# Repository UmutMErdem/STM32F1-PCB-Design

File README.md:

# STM32F1-PCB-Design
In this repo, there is a STM32F103 PCB design project that I developed on KiCad for educational purposes.

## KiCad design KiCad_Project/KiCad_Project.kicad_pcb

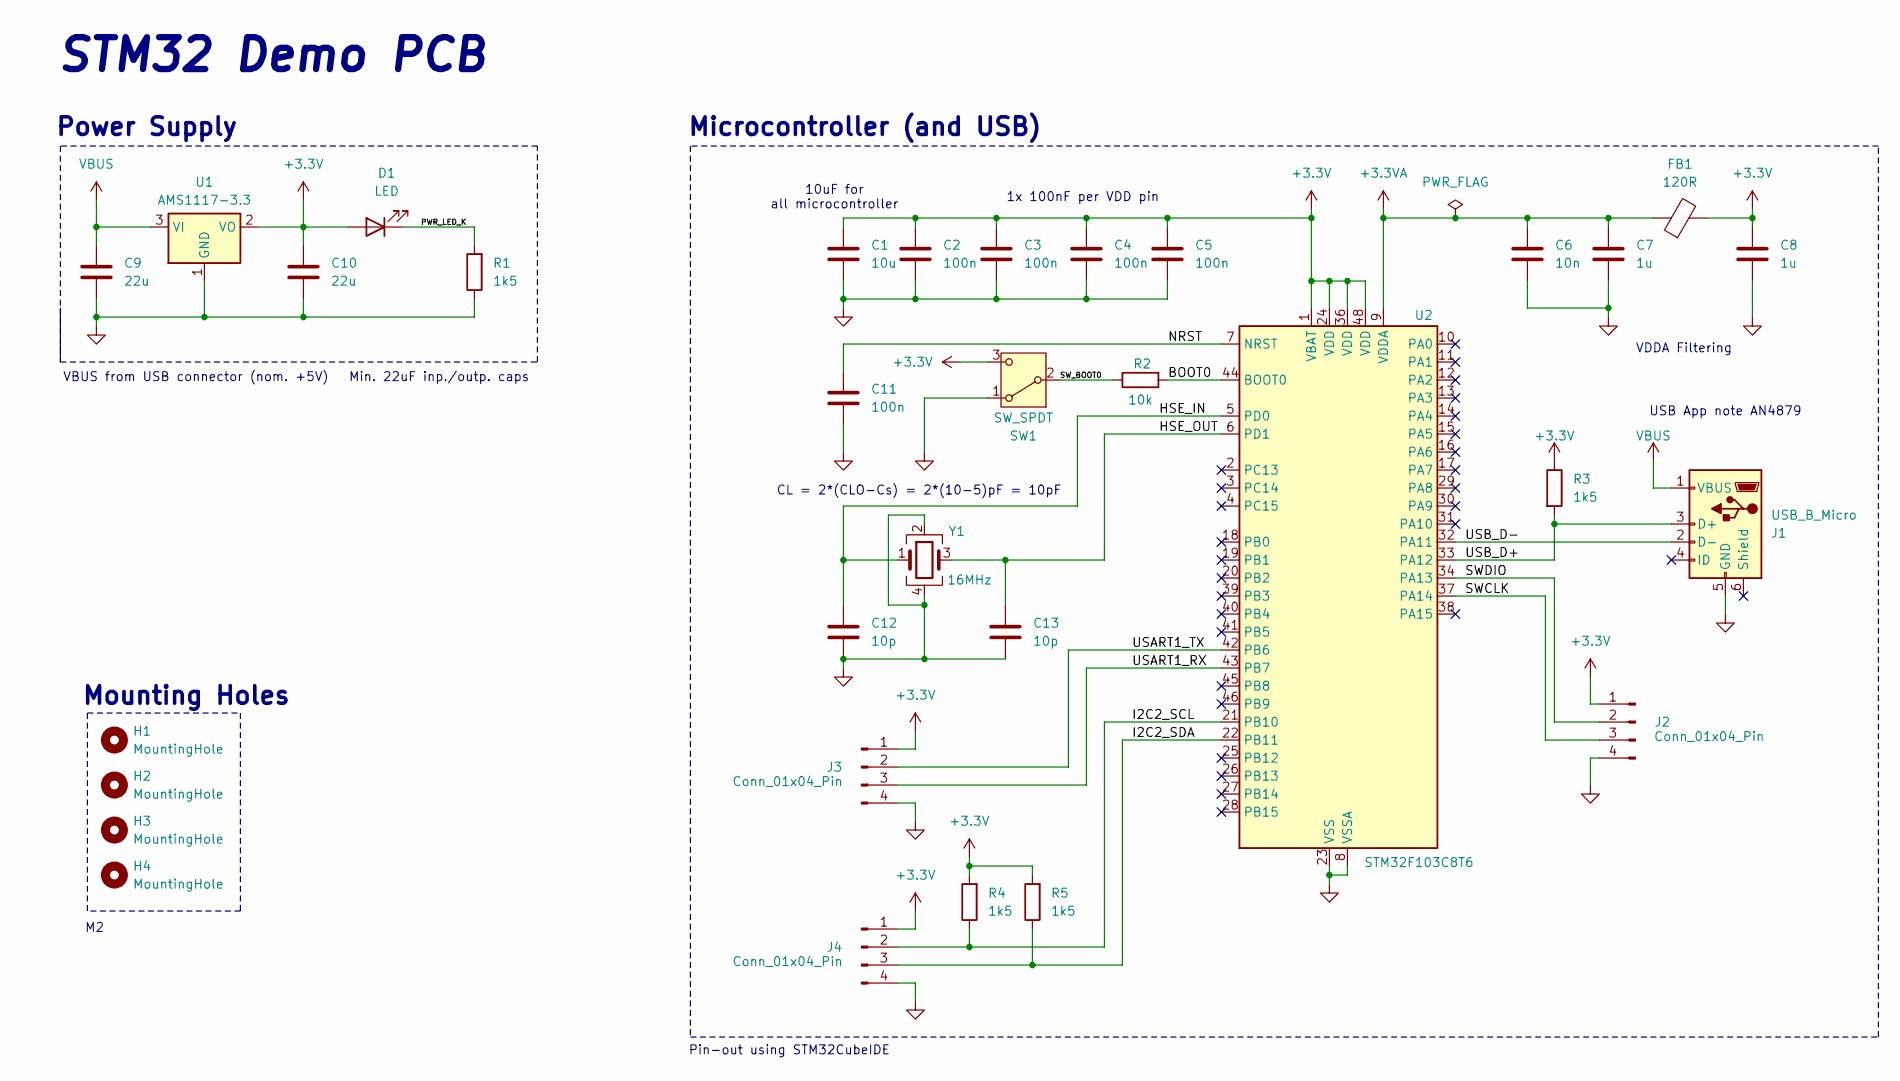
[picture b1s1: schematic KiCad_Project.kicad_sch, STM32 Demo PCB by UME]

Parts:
C1: 10u; C_0603_1608Metric
C2, C3, C4, C5, C11: 100n; C_0402_1005Metric
C6: 10n; C_0402_1005Metric
C7, C8: 1u; C_0402_1005Metric
C9, C10: 22u; C_0805_2012Metric
C12, C13: 10p; C_0402_1005Metric
D1: LED; LED_0603_1608Metric
FB1: 120R; L_0603_1608Metric
H1, H2, H3, H4: MountingHole; MountingHole_2.2mm_M2
J1: USB_B_Micro; USB_Micro-B_Wuerth_629105150521
J2, J3, J4: Conn_01x04_Pin; PinHeader_1x04_P2.54mm_Vertical
R1, R3, R4, R5: 1k5; R_0402_1005Metric
R2: 10k; R_0402_1005Metric
SW1: SW_SPDT; SW_SPDT_PCM12
U1: AMS1117-3.3; SOT-223-3_TabPin2
U2: STM32F103C8T6; LQFP-48_7x7mm_P0.5mm
Y1: 16MHz; Crystal_SMD_3225-4Pin_3.2x2.5mm

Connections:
+3.3V: C1.1, C2.1, C3.1, C4.1, C5.1, C8.1, C10.1, D1.2 (A), FB1.2, J2.1, J3.1, J4.1, R3.1, R4.2, R5.2, SW1.3 (C), U1.2 (VO), U2.1 (VBAT), U2.24 (VDD), U2.36 (VDD), U2.48 (VDD)
+3.3VA: C6.1, C7.1, FB1.1, U2.9 (VDDA)
/BOOT0: R2.2, U2.44 (BOOT0)
/HSE_IN: C12.1, U2.5 (PD0), Y1.1
/HSE_OUT: C13.1, U2.6 (PD1), Y1.3
/I2C2_SCL: J4.2, R4.1, U2.21 (PB10)
/I2C2_SDA: J4.3, R5.1, U2.22 (PB11)
/NRST: C11.1, U2.7 (NRST)
/PWR_LED_K: D1.1 (K), R1.2
/SWCLK: J2.3, U2.37 (PA14)
/SWDIO: J2.2, U2.34 (PA13)
/SW_BOOT0: R2.1, SW1.2 (B)
/USART1_RX: J3.3, U2.43 (PB7)
/USART1_TX: J3.2, U2.42 (PB6)
/USB_D+: J1.3 (D+), R3.2, U2.33 (PA12)
/USB_D-: J1.2 (D-), U2.32 (PA11)
GND: C1.2, C2.2, C3.2, C4.2, C5.2, C6.2, C7.2, C8.2, C9.2, C10.2, C11.2, C12.2, C13.2, J1.5 (GND), J2.4, J3.4, J4.4, R1.1, SW1.1 (A), U1.1 (GND), U2.8 (VSSA), U2.23 (VSS), U2.35 (VSS), U2.47 (VSS), Y1.2, Y1.4
VBUS: C9.1, J1.1 (VBUS), U1.3 (VI)

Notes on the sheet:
10uF for all microcontroller
CL = 2*(CLO-Cs) = 2*(10-5)pF = 10pF
Mounting Holes
Pin-out using STM32CubeIDE
USB App note AN4879
VBUS from USB connector (nom. +5V) Min. 22uF inp./outp. caps
1x 100nF per VDD pin
Microcontroller (and USB)
Power Supply
VDDA Filtering
STM32 Demo PCB

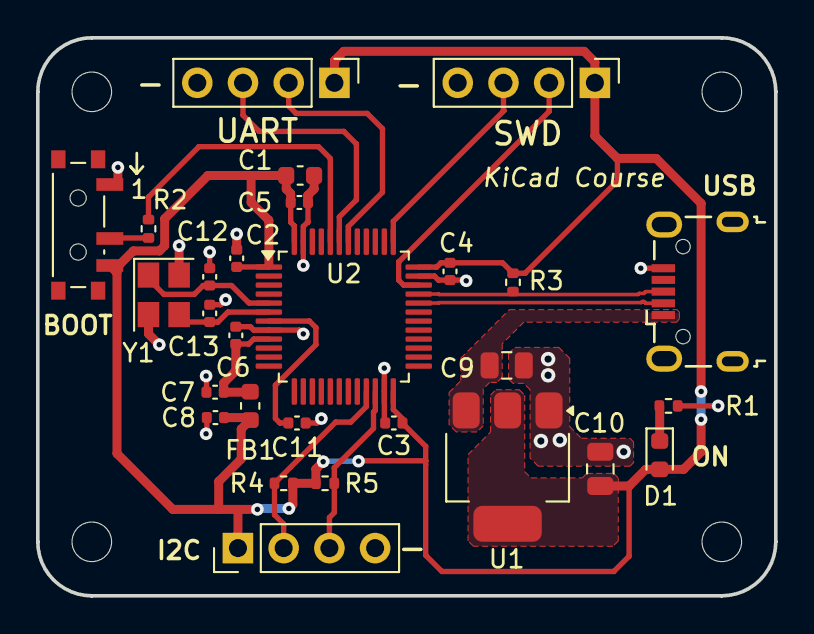
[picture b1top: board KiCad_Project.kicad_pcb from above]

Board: 2 copper layers, 41.0 x 31.0 mm, 32 parts (0 on the bottom side), 18 nets.

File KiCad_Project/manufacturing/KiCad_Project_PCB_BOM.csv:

"Reference","Value","Datasheet","Footprint","Qty","DNP"
"C1","10u","~","Capacitor_SMD:C_0603_1608Metric","1",""
"C2,C3,C4,C5,C11","100n","~","Capacitor_SMD:C_0402_1005Metric","5",""
"C6","10n","~","Capacitor_SMD:C_0402_1005Metric","1",""
"C7,C8","1u","~","Capacitor_SMD:C_0402_1005Metric","2",""
"C9,C10","22u","~","Capacitor_SMD:C_0805_2012Metric","2",""
"C12,C13","10p","~","Capacitor_SMD:C_0402_1005Metric","2",""
"D1","LED","~","LED_SMD:LED_0603_1608Metric","1",""
"FB1","120R","~","Inductor_SMD:L_0603_1608Metric","1",""
"J1","USB_B_Micro","~","Connector_USB:USB_Micro-B_Wuerth_629105150521","1",""
"J2,J3,J4","Conn_01x04_Pin","~","Connector_PinHeader_2.54mm:PinHeader_1x04_P2.54mm_Vertical","3",""
"R1,R3,R4,R5","1k5","~","Resistor_SMD:R_0402_1005Metric","4",""
"R2","10k","~","Resistor_SMD:R_0402_1005Metric","1",""
"SW1","SW_SPDT","~","Button_Switch_SMD:SW_SPDT_PCM12","1",""
"U1","AMS1117-3.3","http://www.advanced-monolithic.com/pdf/ds1117.pdf","Package_TO_SOT_SMD:SOT-223-3_TabPin2","1",""
"U2","STM32F103C8T6","https://www.st.com/resource/en/datasheet/stm32f103c8.pdf","Package_QFP:LQFP-48_7x7mm_P0.5mm","1",""
"Y1","16MHz","~","Crystal:Crystal_SMD_3225-4Pin_3.2x2.5mm","1",""

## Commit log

2024-09-30 addition commit
    Kicad project, block diagram, MCU pin map and manufacturing files are added.
